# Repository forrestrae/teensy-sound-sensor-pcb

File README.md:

# Sound Sensor Teensy Carrier

A KiCad 9.0 carrier board for the Teensy 4.x microcontroller, designed for real-time audio sensing with USB-C Power Delivery input, 4S Li-ion battery management, I2S MEMS microphone, and LED lighting outputs.

## Features

- **USB-C Power Delivery** — TPS25751 PD controller with EEPROM configuration; accepts standard 5 V USB or negotiated PD voltages
- **4S Li-ion Battery System** — BQ25798 charger, BQ7791500 multi-cell protection (30 A rated), and Infineon N-channel disconnect FET
- **Regulated Power Rails** — 5 V and 3.3 V via TPS54538 synchronous buck converter
- **I2S MEMS Microphone** — TDK ICS-43434 with direct I2S2 connection to Teensy
- **Dual LED Drivers** — TPS923652 (white, ADIM + PWM) and TPS92200D2 (UV-A 3535, PWM)
- **Multi-board panel** — PCB ships as a panel; individual sub-boards extracted with kikit

## Hardware Overview

### Schematic Architecture

The design uses KiCad hierarchical sheets:

| Page | Sub-sheet | File |
|------|-----------|------|
| 1 | Top level | `Sound Sensor Teensy Carrier.kicad_sch` |
| 2 | USB-C Connector | `usb-c-connector.kicad_sch` |
| 3 | USB-PD Controller | `usb-pd-controller.kicad_sch` |
| 4 | Battery Charger | `battery-charger.kicad_sch` |
| 5 | DC Converters | `dc-converters.kicad_sch` |
| 6 | MCU | `mcu.kicad_sch` |
| 7 | Battery Protector | `battery_protector.kicad_sch` |
| 8 | Mic Boom | `mic_boom.kicad_sch` |
| 9 | WL-SUMW UV LED Board | `wl-sumw_uv_led_board.kicad_sch` |
| 10 | White LED Board | `white_led_board.kicad_sch` |

### Power Architecture

```
USB-C (5 V–20 V PD)
  └─ TPS25751 USB-PD Controller
       └─ VBUS / +5 V rail
            ├─ TPS54538 Buck → +3.3 V (MCU, logic, microphone)
            └─ BQ25798 Charger → 4S Li-ion pack (14.8 V–16.8 V)
                                    └─ BQ7791500 Protection
```

### Key Components

| Function | Part | Manufacturer |
|----------|------|--------------|
| USB-PD Controller | TPS25751DREFR | Texas Instruments |
| PD Config EEPROM | 24LC256-I/SN | Microchip |
| Battery Charger | BQ25798RQMR | Texas Instruments |
| Battery Protector | BQ7791500PWR | Texas Instruments |
| Disconnect FET | IQDH35N03LM5ATMA1 | Infineon |
| NTC Thermistor | 103AT-2 (10 kΩ) | Semitec |
| Buck Converter | TPS54538RQFR | Texas Instruments |
| MEMS Microphone | ICS-43434 | TDK |
| White LED Driver | TPS923652DRRR | Texas Instruments |
| UV LED Driver | TPS92200D2DDCR | Texas Instruments |

### MCU Connections (Teensy 4.x)

| Signal | Teensy Interface | Description |
|--------|-----------------|-------------|
| `I2S.BCLK` / `SD` / `WS` | I2S2 | ICS-43434 microphone |
| `MCU_I2C.SCL/SDA/IRQ` | I2C | Charger + PD controller |
| `LED.ONSET_EN/ADIM` | PWM | White LED onset channel |
| `LED.BEAT1_EN/ADIM` | PWM | White LED beat channel 1 |
| `LED.BEAT2_EN/ADIM` | PWM | White LED beat channel 2 |

## Repository Structure

```
Sound Sensor Teensy Carrier Kicad/
├── Sound Sensor Teensy Carrier.kicad_pro   # Project file
├── Sound Sensor Teensy Carrier.kicad_pcb   # PCB layout (panel)
├── Sound Sensor Teensy Carrier.kicad_sch   # Top-level schematic
├── battery-charger.kicad_sch
├── battery_protector.kicad_sch
├── dc-converters.kicad_sch
├── mcu.kicad_sch
├── mic_boom.kicad_sch
├── usb-c-connector.kicad_sch
├── usb-pd-controller.kicad_sch
├── white_led_board.kicad_sch
├── wl-sumw_uv_led_board.kicad_sch
├── seperate.zsh                            # kikit panel extraction script
├── ibom.config.ini                         # Interactive BOM config
└── freerouting.dsn                         # Freerouting export
```

## Tools & Dependencies

| Tool | Purpose | Install |
|------|---------|---------|
| [KiCad 9.0](https://www.kicad.org/) | EDA (schematic + layout) | kicad.org |
| [kikit](https://github.com/yaqwsx/KiKit) | Panel sub-board extraction | `pip install kikit` |
| [InteractiveHtmlBom](https://github.com/openscopeproject/InteractiveHtmlBom) | BOM generation | KiCad plugin manager |

## Sub-board Extraction

The PCB is laid out as a panel. `seperate.zsh` uses `kikit separate` to extract individual sub-boards by board-array reference designator into `output/<name>/`:

```zsh
./seperate.zsh
```

Edit the script to enable/disable specific boards (B1–B6). Extracted boards are written to `output/<board-name>/<board-name>.kicad_pcb`.

## BOM Generation

Open the project in KiCad and run the **Interactive HTML BOM** plugin. Output lands in `bom/ibom.html` per `ibom.config.ini`. Key BOM fields: Value, Footprint, MPN, Manufacturer, Datasheet, Category.

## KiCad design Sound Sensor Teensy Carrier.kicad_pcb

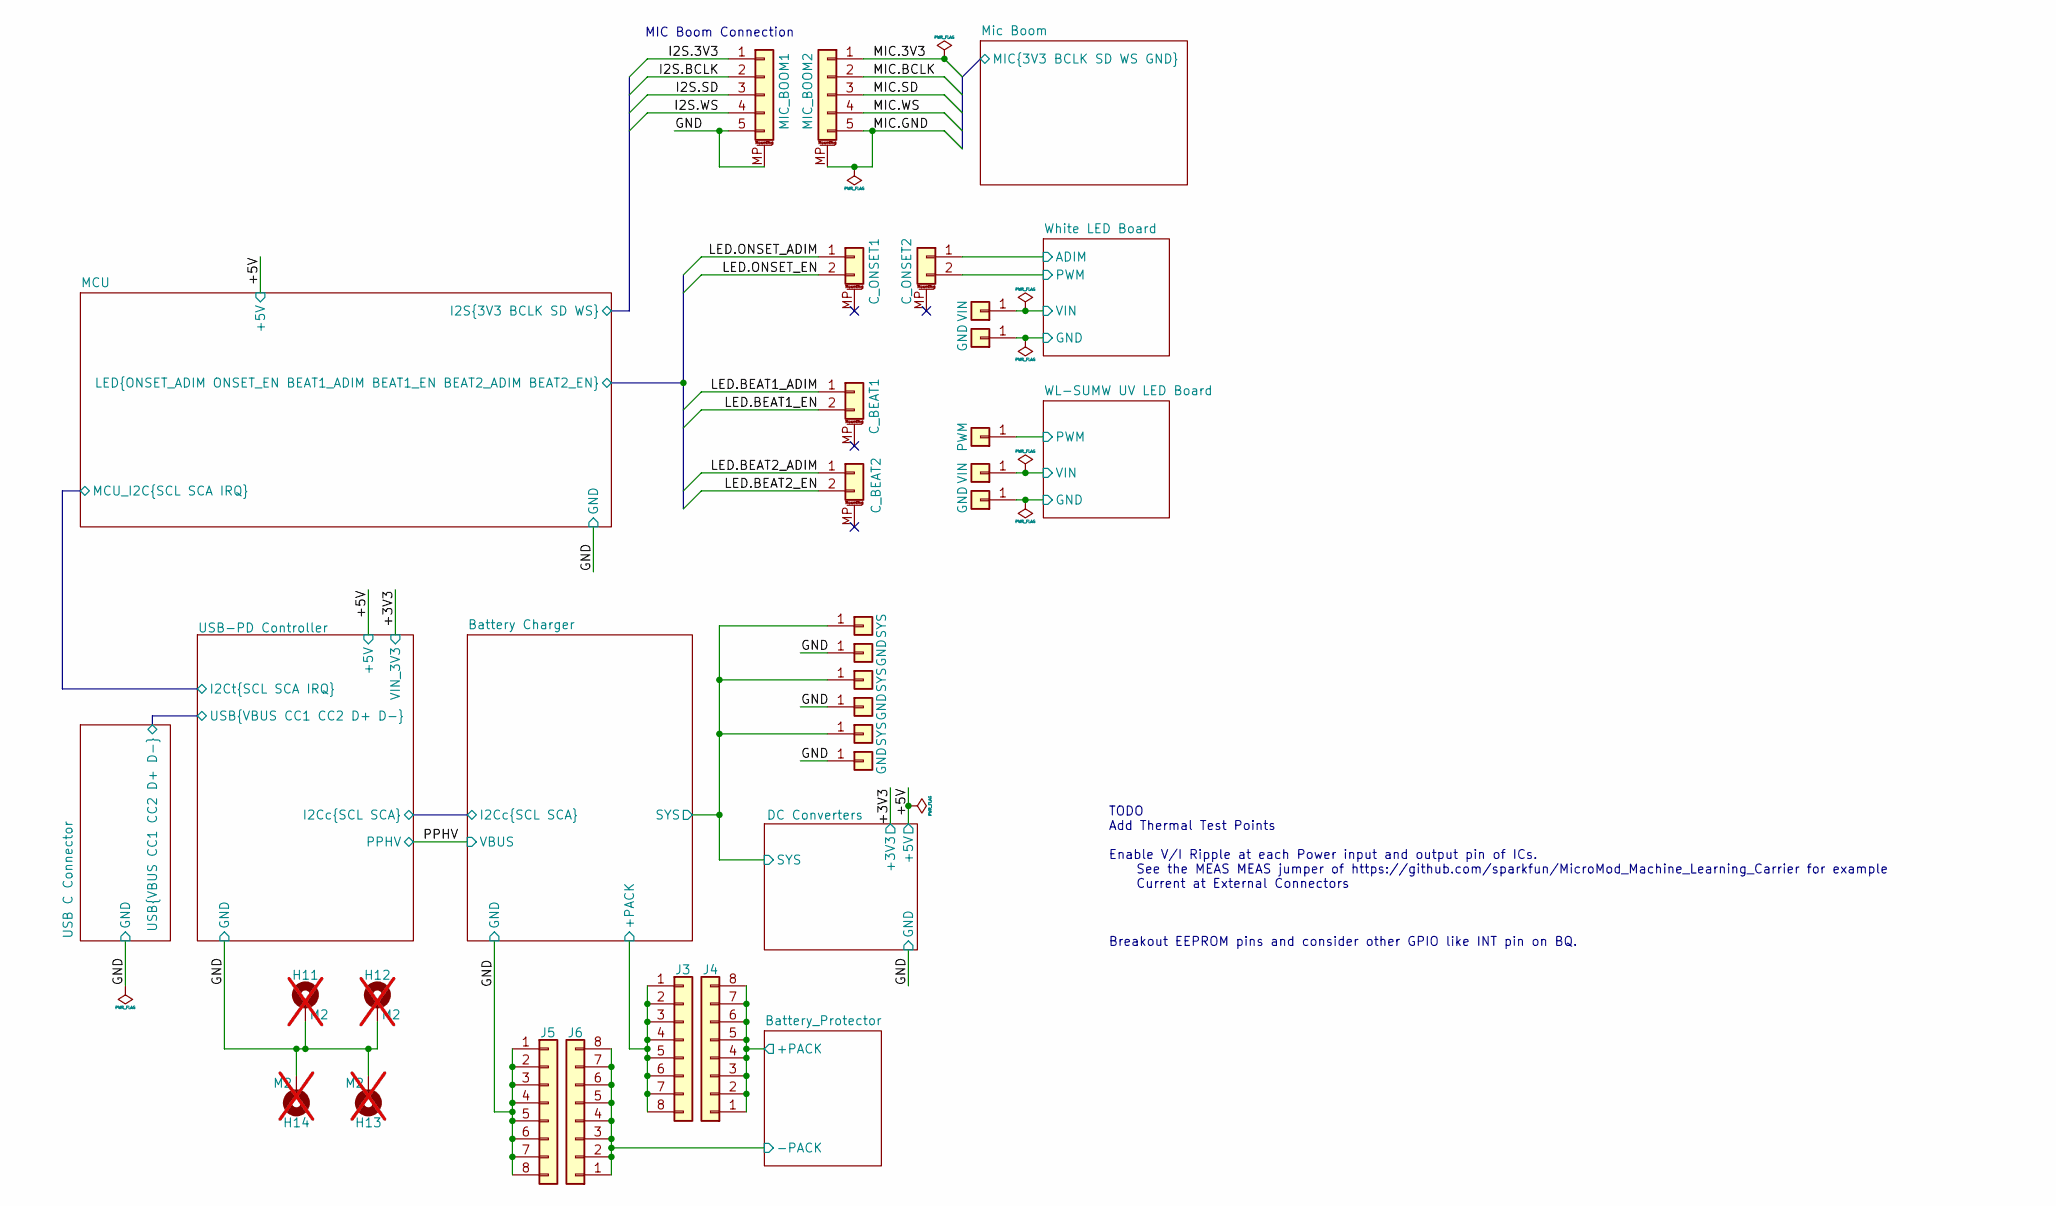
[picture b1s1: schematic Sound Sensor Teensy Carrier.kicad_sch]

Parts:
C_BEAT1: BEAT1; Molex_Pico-Clasp_203558-0207_1x02-1MP_P1.00mm_Horizontal; MPN 203558-0207; Mouser SPN 538-203558-0207
C_BEAT2: BEAT2; Molex_Pico-Clasp_203558-0207_1x02-1MP_P1.00mm_Horizontal; MPN 203558-0207; Mouser SPN 538-203558-0207
C_ONSET1, C_ONSET2: ONSET; Molex_Pico-Clasp_203558-0207_1x02-1MP_P1.00mm_Horizontal; MPN 203558-0207; Mouser SPN 538-203558-0207
H3, H5, H7: SYS; SolderWirePad_1x01_SMD_2x4mm
H4, H6, H8, H24, H26: GND; SolderWirePad_1x01_SMD_2x4mm
H11, H12, H13, H14: M2; StandOff_M2x5mm; MPN 971050244; Mouser SPN 710-971050244; not fitted
H23, H25: VIN; SolderWirePad_1x01_SMD_2x4mm
H27: PWM; SolderWirePad_1x01_SMD_1.5x3mm
J3: +PACK; SAMTEC_TMMH-104-05-F-DV; MPN TMMH-104-05-F-DV; Mouser SPN 200-TMMH10405FDV
J4: +PACK; SAMTEC_CLT-104-02-F-D; MPN CLT-104-02-F-D; Mouser SPN 200-CLT10402FD
J5: -PACK; SAMTEC_TMMH-104-05-F-DV; MPN TMMH-104-05-F-DV; Mouser SPN 200-TMMH10405FDV
J6: -PACK; SAMTEC_CLT-104-02-F-D; MPN CLT-104-02-F-D; Mouser SPN 200-CLT10402FD
MIC_BOOM1: MIC; Molex_Pico-Clasp_202396-0507_1x05-1MP_P1.00mm_Horizontal; MPN 203562-0505; Mouser SPN 538-203562-0505
MIC_BOOM2: MIC; Molex_Pico-Clasp_501331-0507_1x05-1MP_P1.00mm_Vertical; MPN 504449-0507; Mouser SPN 538-504449-0507

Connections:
/Battery Charger/+PACK: J3.1, J3.2, J3.3, J3.4, J3.5, J3.6, J3.7, J3.8; also elsewhere on the board
/Battery Charger/SYS: H3.1, H5.1, H7.1; also elsewhere on the board
/Battery_Protector/+PACK: J4.1, J4.2, J4.3, J4.4, J4.5, J4.6, J4.7, J4.8; also elsewhere on the board
/Battery_Protector/-PACK: J6.1, J6.2, J6.3, J6.4, J6.5, J6.6, J6.7, J6.8; also elsewhere on the board
/GND: H4.1, H6.1, H8.1, H11.1, H12.1, H13.1, H14.1, J5.1, J5.2, J5.3, J5.4, J5.5, J5.6, J5.7, J5.8, MIC_BOOM1.5, MIC_BOOM1.MP (MountPin); also elsewhere on the board
/MCU/I2S.3V3: MIC_BOOM1.1; also elsewhere on the board
/MCU/I2S.BCLK: MIC_BOOM1.2; also elsewhere on the board
/MCU/I2S.SD: MIC_BOOM1.3; also elsewhere on the board
/MCU/I2S.WS: MIC_BOOM1.4; also elsewhere on the board
/MCU/LED.BEAT1_ADIM: C_BEAT1.1; also elsewhere on the board
/MCU/LED.BEAT1_EN: C_BEAT1.2; also elsewhere on the board
/MCU/LED.BEAT2_ADIM: C_BEAT2.1; also elsewhere on the board
/MCU/LED.BEAT2_EN: C_BEAT2.2; also elsewhere on the board
/MCU/LED.ONSET_ADIM: C_ONSET1.1; also elsewhere on the board
/MCU/LED.ONSET_EN: C_ONSET1.2; also elsewhere on the board
/Mic Boom/MIC.3V3: MIC_BOOM2.1; also elsewhere on the board
/Mic Boom/MIC.BCLK: MIC_BOOM2.2; also elsewhere on the board
/Mic Boom/MIC.GND: MIC_BOOM2.5, MIC_BOOM2.MP (MountPin); also elsewhere on the board
/Mic Boom/MIC.SD: MIC_BOOM2.3; also elsewhere on the board
/Mic Boom/MIC.WS: MIC_BOOM2.4; also elsewhere on the board
/WL-SUMW UV LED Board/GND: H26.1; also elsewhere on the board
/WL-SUMW UV LED Board/PWM: H27.1; also elsewhere on the board
/WL-SUMW UV LED Board/VIN: H25.1; also elsewhere on the board
/White LED Board/ADIM: C_ONSET2.1; also elsewhere on the board
/White LED Board/GND: H24.1; also elsewhere on the board
/White LED Board/PWM: C_ONSET2.2; also elsewhere on the board
/White LED Board/VIN: H23.1; also elsewhere on the board

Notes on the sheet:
MIC Boom Connection
TODO Add Thermal Test Points Enable V/I Ripple at each Power input and output pin of ICs. See the MEAS MEAS jumper of https://github.com/sparkfun/MicroMod_Machine_Learning_Carrier for example Current at External Connectors Breakout EEPROM pins and consider other GPIO like INT pin on BQ.

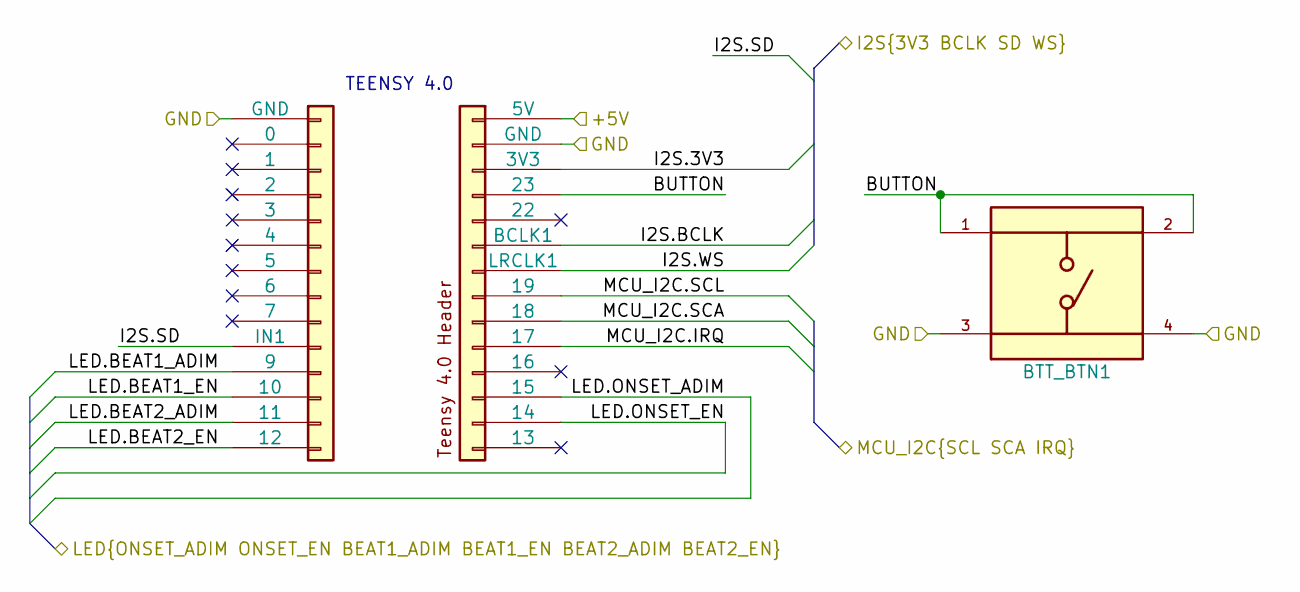
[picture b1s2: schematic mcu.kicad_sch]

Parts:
BTT_BTN1: 13mm; SW_TS02-66-130-BK-260-SCR-D; PARTREV 1.0; Mouser SPN 179-TS0266130BK260SC
C_TEENSY1: Teensy_4.0_Pin_Header; MPN SLW-150-01-G-S

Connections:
/+5V: C_TEENSY1.5V; also elsewhere on the board
/GND: BTT_BTN1.3, BTT_BTN1.4, C_TEENSY1.G0 (GND), C_TEENSY1.G1 (GND); also elsewhere on the board
/MCU/BUTTON: BTT_BTN1.1, BTT_BTN1.2, C_TEENSY1.23
/MCU/I2S.3V3: C_TEENSY1.3V3; also elsewhere on the board
/MCU/I2S.BCLK: C_TEENSY1.21 (BCLK1); also elsewhere on the board
/MCU/I2S.SD: C_TEENSY1.8 (IN1); also elsewhere on the board
/MCU/I2S.WS: C_TEENSY1.20 (LRCLK1); also elsewhere on the board
/MCU/LED.BEAT1_ADIM: C_TEENSY1.9; also elsewhere on the board
/MCU/LED.BEAT1_EN: C_TEENSY1.10; also elsewhere on the board
/MCU/LED.BEAT2_ADIM: C_TEENSY1.11; also elsewhere on the board
/MCU/LED.BEAT2_EN: C_TEENSY1.12; also elsewhere on the board
/MCU/LED.ONSET_ADIM: C_TEENSY1.15; also elsewhere on the board
/MCU/LED.ONSET_EN: C_TEENSY1.14; also elsewhere on the board
/MCU/MCU_I2C.IRQ: C_TEENSY1.17; also elsewhere on the board
/MCU/MCU_I2C.SCA: C_TEENSY1.18; also elsewhere on the board
/MCU/MCU_I2C.SCL: C_TEENSY1.19; also elsewhere on the board

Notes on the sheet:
TEENSY 4.0

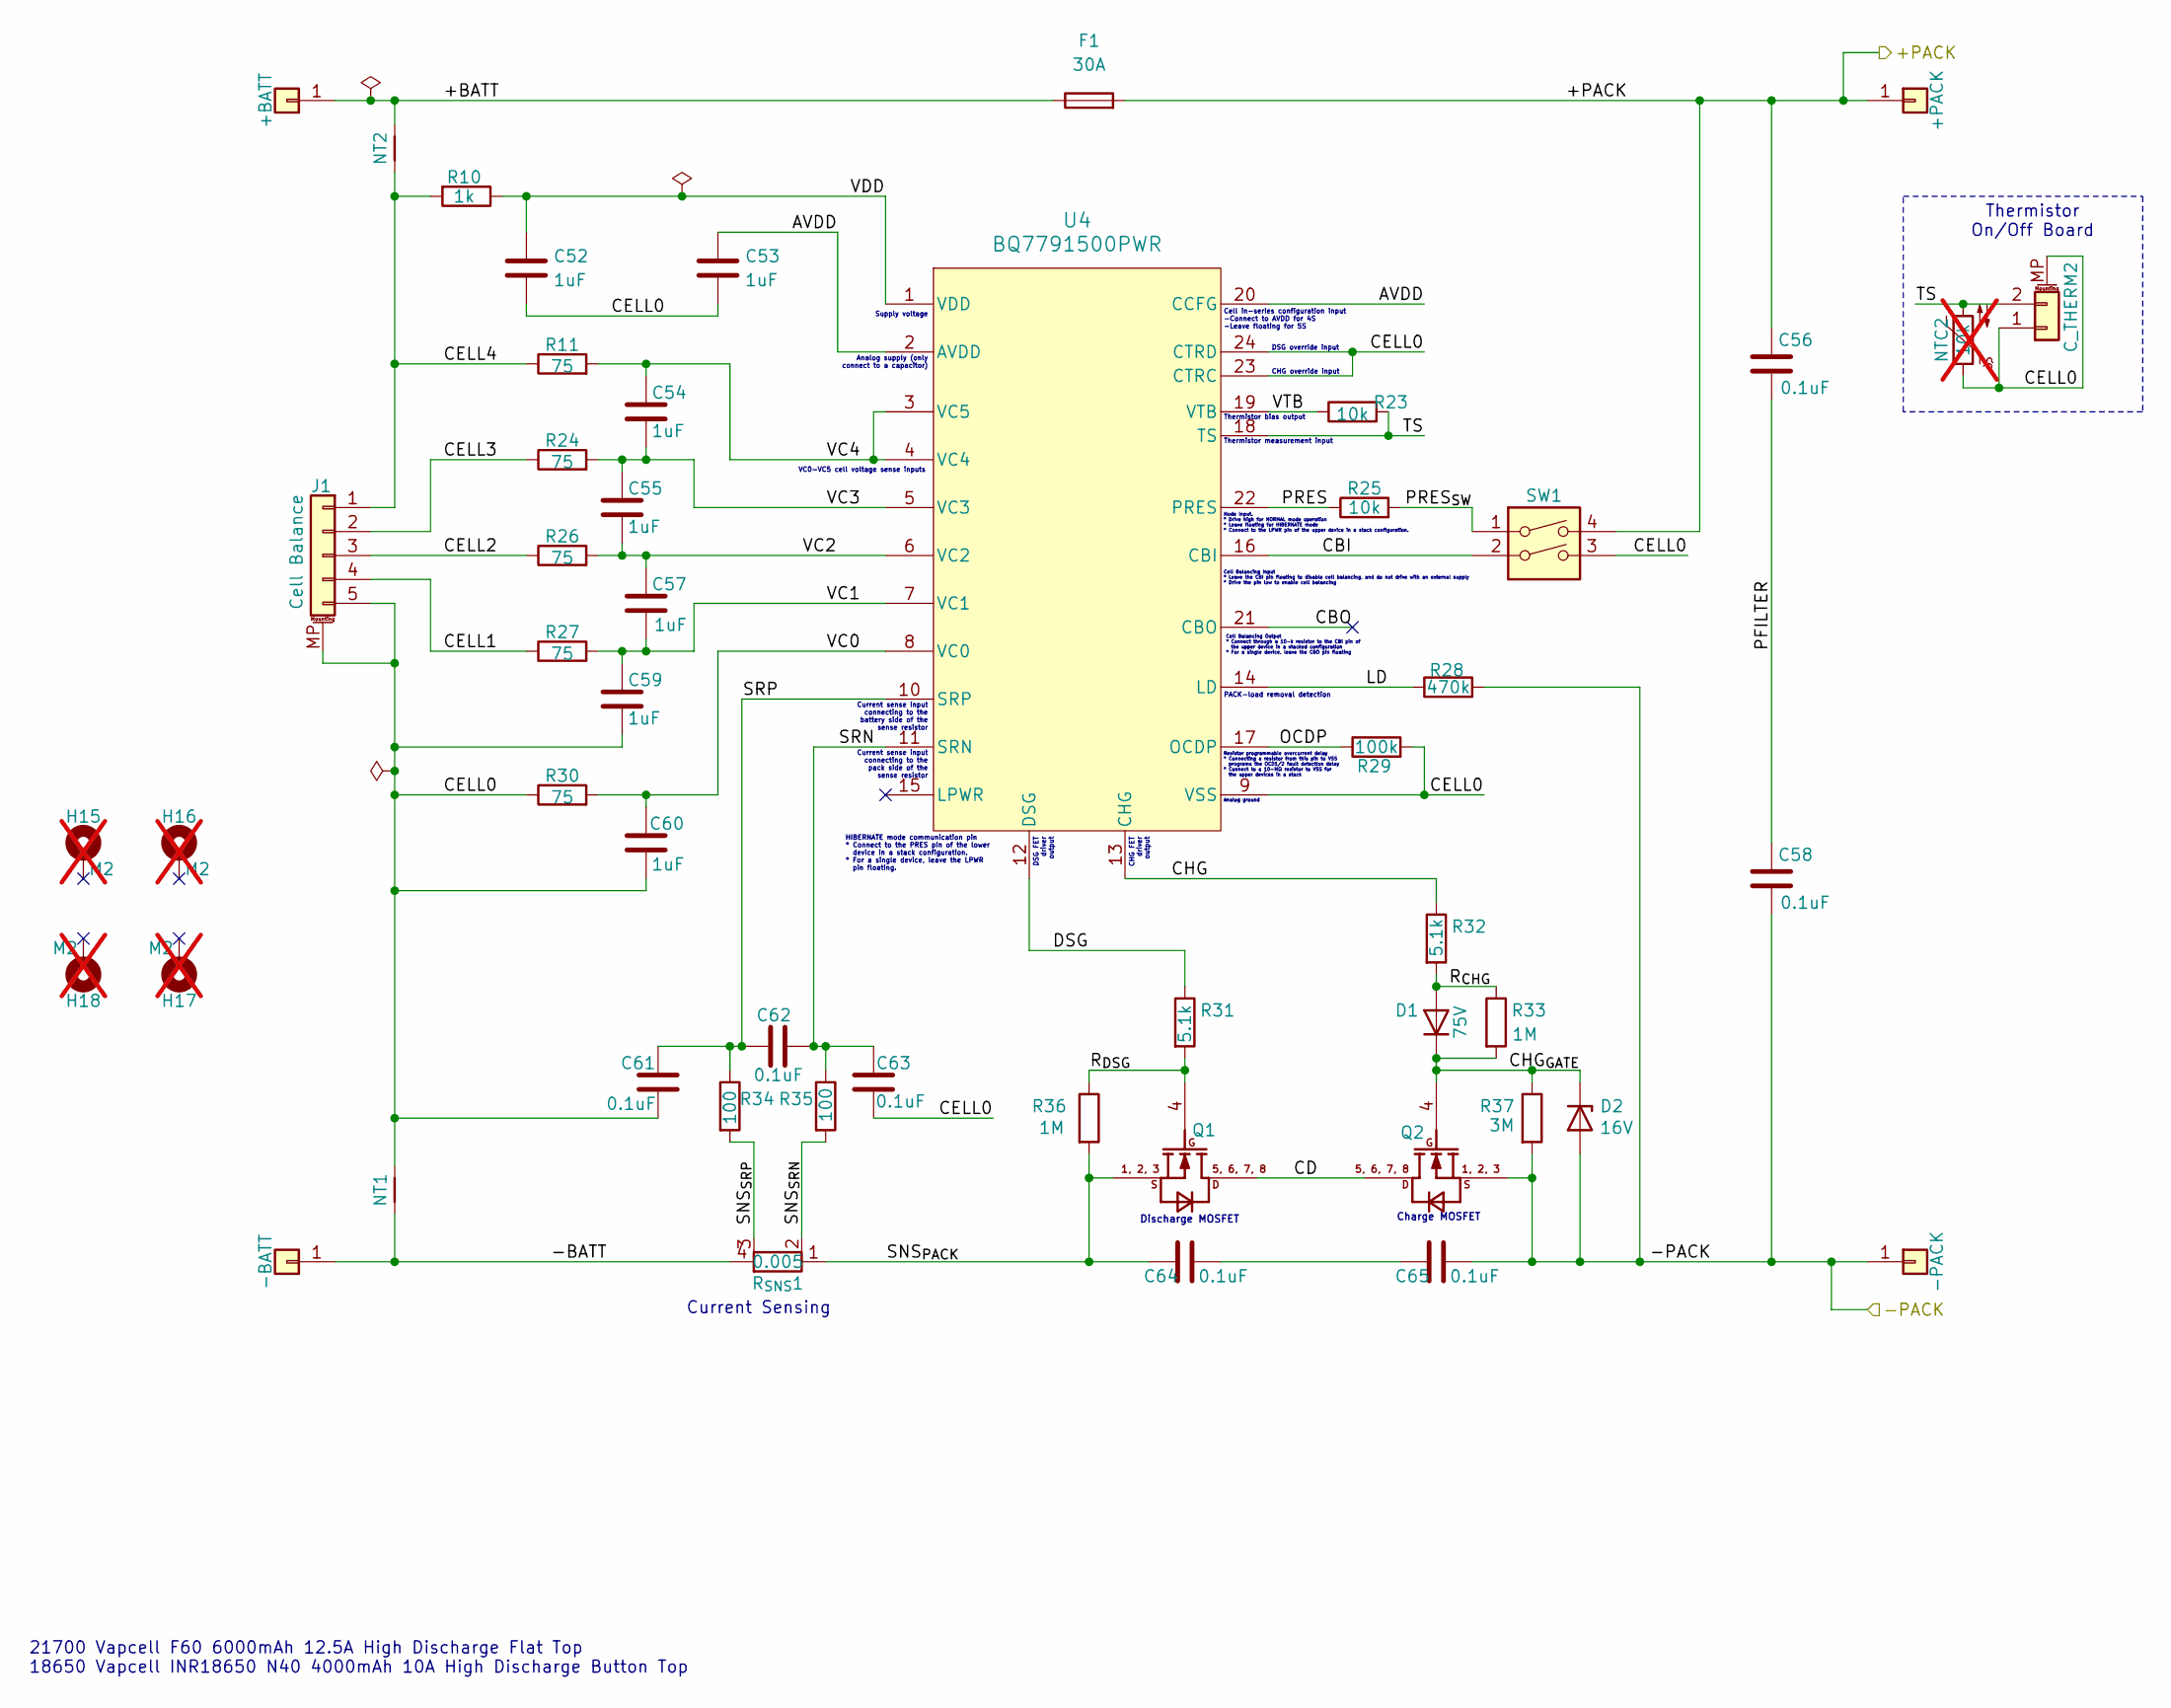
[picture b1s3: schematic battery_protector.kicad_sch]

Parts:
C52, C53, C54, C55, C57, C59, C60: 1uF; C_0603_1608Metric; MPN 06035C105KAT2A; Farnell SPN 4155078
C56, C58, C61, C62, C63, C64, C65: 0.1uF; C_0603_1608Metric; MPN GCM188R71H104KA57J; Mouser SPN 81-GCM188R71H104KA7J
C_THERM2: NTC; Molex_Pico-Clasp_203558-0207_1x02-1MP_P1.00mm_Horizontal; MPN 203558-0207; Mouser SPN 538-203558-0207
D1: 75V; D_SOD-323F; MPN CDSF4148; Mouser SPN 750-CDSF4148
D2: 16V; D_SOD-323; MPN BZX384C16-G3-08; Mouser SPN 78-BZX384C16-G3-08
F1: 30A; FUSE_SF-3812FG3000T-2; MPN SF-3812FG3000T-2; Mouser SPN 652-SF-3812FG3000T-2
H1: +BATT; SolderWirePad_1x01_SMD_4x8mm
H2: -BATT; SolderWirePad_1x01_SMD_4x8mm
H9: +PACK; SolderWirePad_1x01_SMD_4x8mm
H10: -PACK; SolderWirePad_1x01_SMD_4x8mm
H15, H16, H17, H18: M2; StandOff_M2x5mm; MPN 971050244; Mouser SPN 710-971050244; not fitted
J1: Cell Balance; Molex_Pico-Clasp_202396-0507_1x05-1MP_P1.00mm_Horizontal; MPN 203562-0505; Mouser SPN 538-203562-0505
NT1, NT2: NetTie_2; NetTie-2_SMD_Pad0.5mm
NTC2: 10k; R_0603_1608Metric; MPN NTCGS163JX103DT8; DigiKey SPN 445-NTCGS163JX103DT8CT-ND; not fitted
Q1, Q2: IQDH35N03LM5; IFX-PG-TSON-8-9-V; MPN IQDH35N03LM5ATMA1; DigiKey SPN 448-IQDH35N03LM5ATMA1TR-ND
R10: 1k; R_0603_1608Metric; MPN RCS06031K00FKEA; DigiKey SPN 541-2788-1-ND
R11, R24, R26, R27, R30: 75; R_0603_1608Metric; MPN RCS060375R0FKEA; Farnell SPN 4140951
R23, R25: 10k; R_0603_1608Metric; MPN RCS060310K0FKEA; Mouser SPN 71-RCS060310K0FKEA
R28: 470k; R_0603_1608Metric; MPN CRCW0603470KFKEA; Farnell SPN 1469814
R29: 100k; R_0603_1608Metric; MPN RCS0603100KFKEA; Mouser SPN 71-RCS0603100KFKEA
R31, R32: 5.1k; R_0603_1608Metric; MPN RCS06035K10FKEA; Farnell SPN 4140947
R33, R36: 1M; R_0603_1608Metric; MPN RCS06031M00FKEA; Farnell SPN 4140931
R34, R35: 100; R_0603_1608Metric; MPN RCS0603100RFKEA; Mouser SPN 71-RCS0603100RFKEA
R37: 3M; R_0603_1608Metric; MPN CRCW06033M00FKEA; Farnell SPN 1469650
R_{SNS}1: 0.005; R_Shunt_Vishay_WSL3637_9194Metric_T2.18mm; MPN WSL36375L000DEA; Farnell SPN 4552590
SW1: DIP; SW_DIP_SPSTx02_Slide_Omron_A6H-2101_W6.15mm_P1.27mm; MPN A6H-2101; Farnell SPN 1960885
U4: BQ7791500PWR; PW24_TEX; MPN BQ7791500PWR; DigiKey SPN 296-50995-2-ND

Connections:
/Battery_Protector/+BATT: F1.1, H1.1, NT2.2
/Battery_Protector/+PACK: C56.1, F1.2, H9.1, SW1.4; also elsewhere on the board
/Battery_Protector/-BATT: H2.1, NT1.1, R_{SNS}1.4
/Battery_Protector/-PACK: C58.2, C65.2, D2.2 (A), H10.1, Q2.1 (SOURCE), Q2.2 (SOURCE), Q2.3 (SOURCE), R28.2, R37.2; also elsewhere on the board
/Battery_Protector/AVDD: C53.1, U4.2 (AVDD), U4.20 (CCFG)
/Battery_Protector/CBI: SW1.2, U4.16 (CBI)
/Battery_Protector/CBO: U4.21 (CBO)
/Battery_Protector/CD: Q1.5 (DRAIN), Q1.6 (DRAIN), Q1.7 (DRAIN), Q1.8 (DRAIN), Q2.5 (DRAIN), Q2.6 (DRAIN), Q2.7 (DRAIN), Q2.8 (DRAIN)
/Battery_Protector/CELL0: C52.2, C53.2, C59.2, C60.2, C61.2, C63.1, C_THERM2.1, C_THERM2.MP (MountPin), J1.5, J1.MP (MountPin), NT1.2, NTC2.1, R29.2, R30.1, SW1.3, U4.9 (VSS), U4.23 (CTRC), U4.24 (CTRD)
/Battery_Protector/CELL1: J1.4, R27.1
/Battery_Protector/CELL2: J1.3, R26.1
/Battery_Protector/CELL3: J1.2, R24.1
/Battery_Protector/CELL4: J1.1, NT2.1, R10.2, R11.1
/Battery_Protector/CHG: R32.1, U4.13 (CHG)
/Battery_Protector/CHG_{GATE}: D1.1 (K), D2.1 (K), Q2.4 (GATE), R33.2, R37.1
/Battery_Protector/DSG: R31.1, U4.12 (DSG)
/Battery_Protector/LD: R28.1, U4.14 (LD)
/Battery_Protector/OCDP: R29.1, U4.17 (OCDP)
/Battery_Protector/PFILTER: C56.2, C58.1
/Battery_Protector/PRES: R25.1, U4.22 (PRES)
/Battery_Protector/PRES_{SW}: R25.2, SW1.1
/Battery_Protector/R_{CHG}: D1.2 (A), R32.2, R33.1
/Battery_Protector/R_{DSG}: Q1.4 (GATE), R31.2, R36.1
/Battery_Protector/SNS_{PACK}: C64.1, Q1.1 (SOURCE), Q1.2 (SOURCE), Q1.3 (SOURCE), R36.2, R_{SNS}1.1
/Battery_Protector/SNS_{SRN}: R35.2, R_{SNS}1.2
/Battery_Protector/SNS_{SRP}: R34.2, R_{SNS}1.3
/Battery_Protector/SRN: C62.2, C63.2, R35.1, U4.11 (SRN)
/Battery_Protector/SRP: C61.1, C62.1, R34.1, U4.10 (SRP)
/Battery_Protector/TS: C_THERM2.2, NTC2.2, R23.2, U4.18 (TS)
/Battery_Protector/VC0: C60.1, R30.2, U4.8 (VC0)
/Battery_Protector/VC1: C57.2, C59.1, R27.2, U4.7 (VC1)
/Battery_Protector/VC2: C55.2, C57.1, R26.2, U4.6 (VC2)
/Battery_Protector/VC3: C54.2, C55.1, R24.2, U4.5 (VC3)
/Battery_Protector/VC4: C54.1, R11.2, U4.3 (VC5), U4.4 (VC4)
/Battery_Protector/VDD: C52.1, R10.1, U4.1 (VDD)
/Battery_Protector/VTB: R23.1, U4.19 (VTB)
unnamed: C64.2, C65.1

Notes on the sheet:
Thermistor On/Off Board
Cell Balancing Output * Connect through a 10-k resistor to the CBI pin of the upper device in a stacked configuration * For a single device, leave the CBO pin floating
Analog ground
DSG override input
HIBERNATE mode communication pin * Connect to the PRES pin of the lower device in a stack configuration. * For a single device, leave the LPWR pin floating.
Analog supply (only connect to a capacitor)
PACK-load removal detection
Resistor programmable overcurrent delay * Connecting a resistor from this pin to VSS programs the OCD1/2 fault detection delay * Connect to a 10-MΩ resistor to VSS for the upper devices in a stack
Current Sensing
21700 Vapcell F60 6000mAh 12.5A High Discharge Flat Top 18650 Vapcell INR18650 N40 4000mAh 10A High Discharge Button Top
DSG FET driver output
Cell in-series configuration input -Connect to AVDD for 4S -Leave floating for 5S
Charge MOSFET
Cell Balancing Input * Leave the CBI pin floating to disable cell balancing, and do not drive with an external supply * Drive the pin low to enable cell balancing
Discharge MOSFET
Thermistor measurement input
CHG FET driver output
Mode Input. * Drive high for NORMAL mode operation * Leave floating for HIBERNATE mode * Connect to the LPWR pin of the upper device in a stack configuration.
Current sense input connecting to the pack side of the sense resistor
VC0-VC5 cell voltage sense inputs
Current sense input connecting to the battery side of the sense resistor
Supply voltage
Thermistor bias output
CHG override input

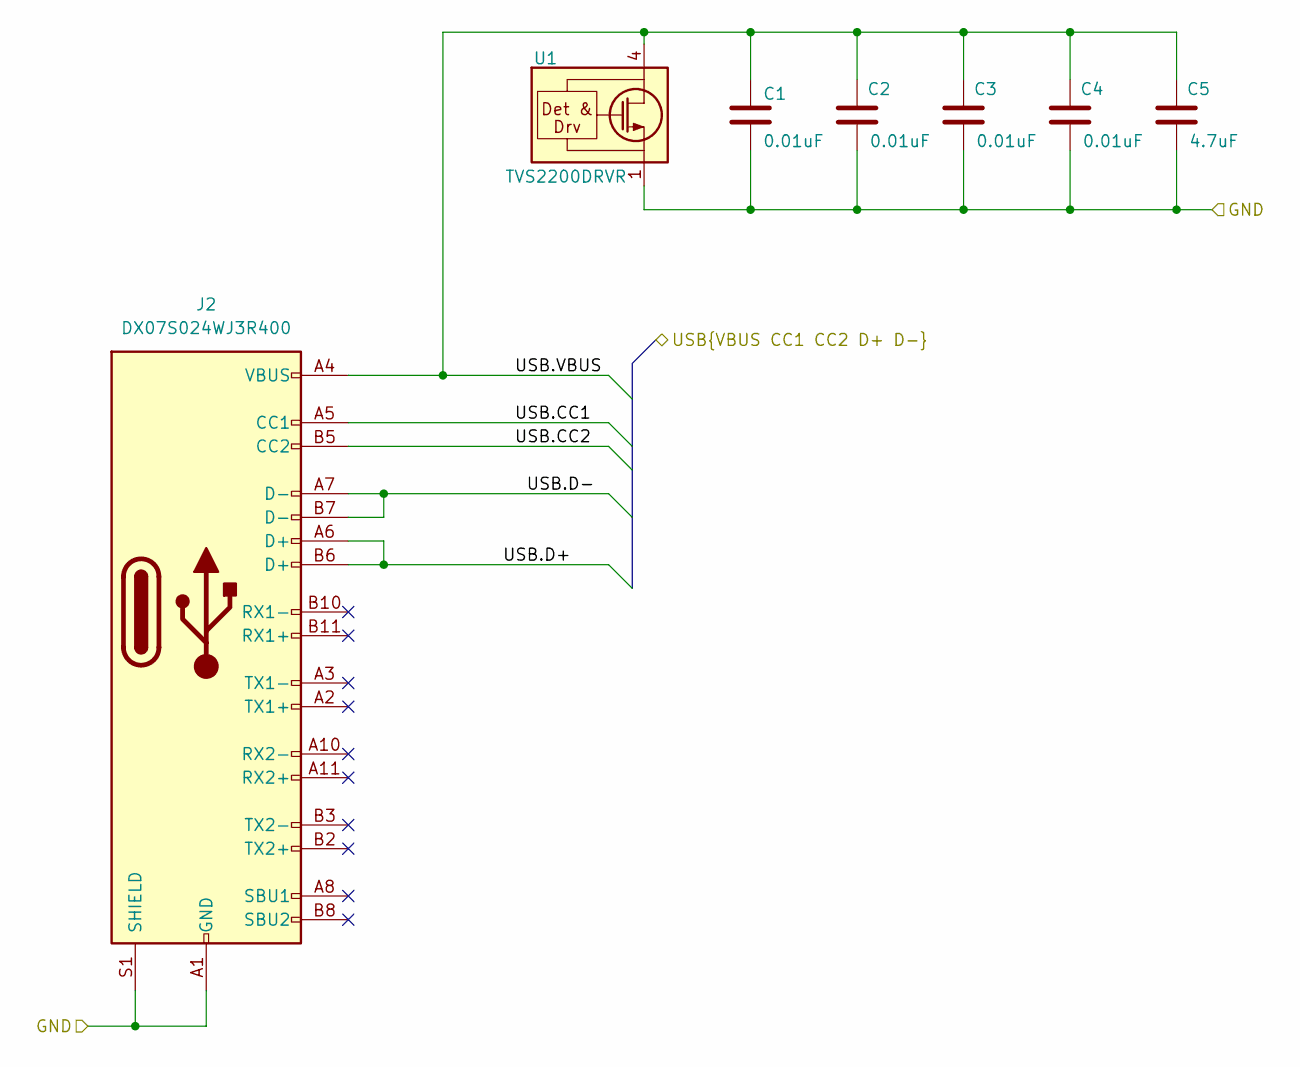
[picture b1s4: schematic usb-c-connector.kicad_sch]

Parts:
C1, C2, C3, C4: 0.01uF; C_0603_1608Metric; MPN GCM1885C1H103GA16D; Mouser SPN 81-GCM1885C1H103GA6D
C5: 4.7uF; C_0603_1608Metric; MPN GRM188R6YA475KE15D; Mouser SPN 81-GRM188R6YA475KE5D
J2: DX07S024WJ3R400; USB_C_Receptacle_JAE_DX07S024WJ3R400; MPN DX07S024WJ3R400; Mouser SPN 656-DX07S0024WJ3R400
U1: TVS2200DRVR; WSON-6-1EP_2x2mm_P0.65mm_EP1x1.6mm; MPN TVS2200DRVR; Mouser SPN 595-TVS2200DRVR

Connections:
/GND: C1.2, C2.2, C3.2, C4.2, C5.2, J2.A1 (GND), J2.A12 (GND), J2.B1 (GND), J2.B12 (GND), J2.S1 (SHIELD), U1.1 (GND), U1.2 (GND), U1.3 (GND), U1.7 (GND); also elsewhere on the board
/USB C Connector/USB.CC1: J2.A5 (CC1); also elsewhere on the board
/USB C Connector/USB.CC2: J2.B5 (CC2); also elsewhere on the board
/USB C Connector/USB.D+: J2.A6 (D+), J2.B6 (D+); also elsewhere on the board
/USB C Connector/USB.D-: J2.A7 (D-), J2.B7 (D-); also elsewhere on the board
/USB C Connector/USB.VBUS: C1.1, C2.1, C3.1, C4.1, C5.1, J2.A4 (VBUS), J2.A9 (VBUS), J2.B4 (VBUS), J2.B9 (VBUS), U1.4 (IN), U1.5 (IN), U1.6 (IN); also elsewhere on the board

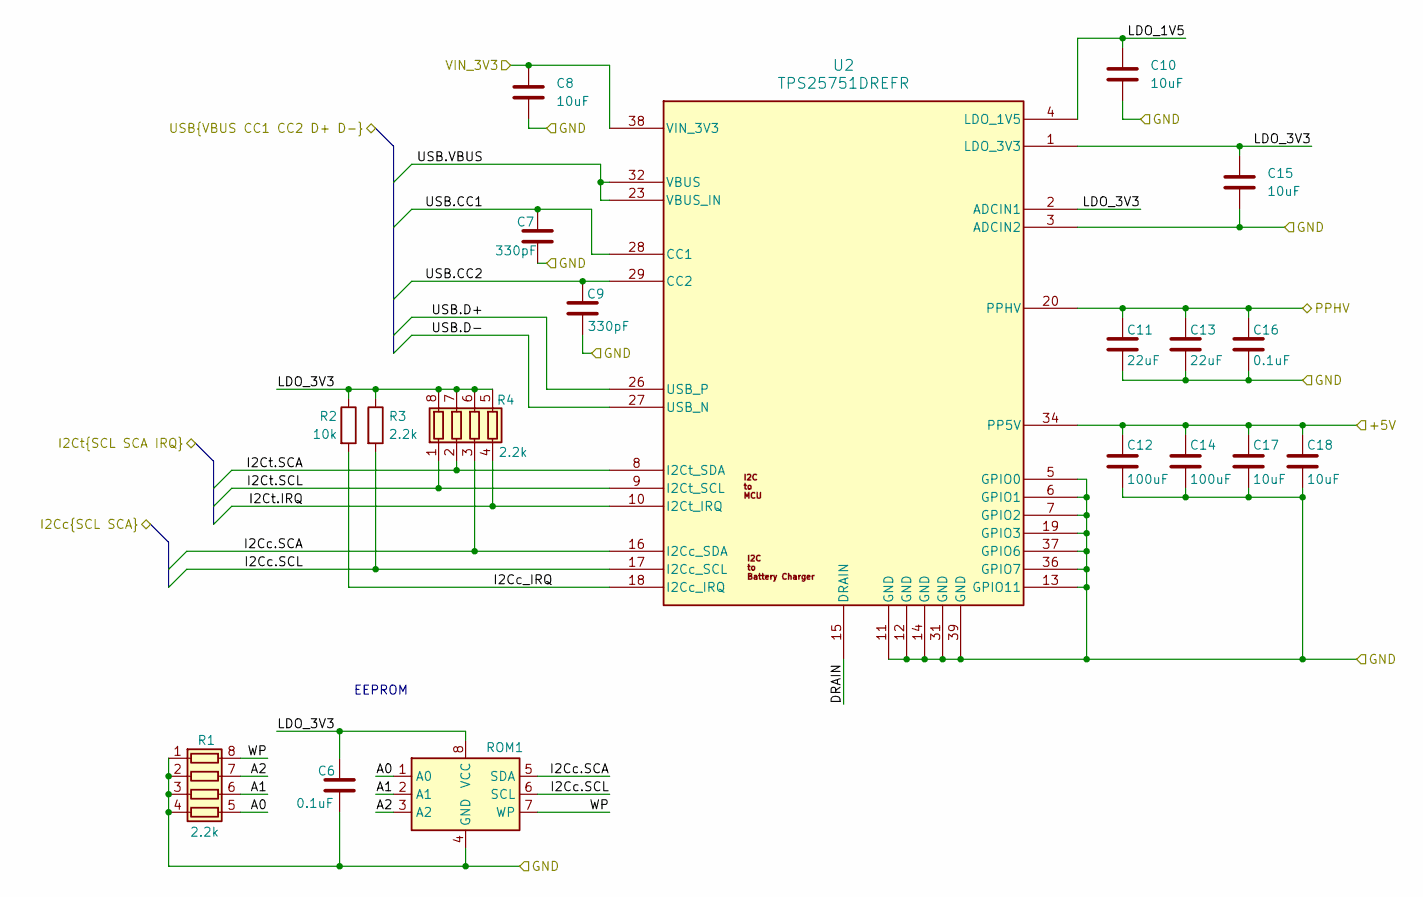
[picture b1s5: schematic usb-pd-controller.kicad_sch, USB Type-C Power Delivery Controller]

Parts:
C6, C16: 0.1uF; C_0603_1608Metric; MPN GCM188R71H104KA57J; Mouser SPN 81-GCM188R71H104KA7J
C7, C9: 330pF; C_0603_1608Metric; MPN VJ0603A331FXACW1BC; Mouser SPN 77-VJ0603A331FXACBC
C8, C10, C15, C17, C18: 10uF; C_0603_1608Metric; MPN GRM188R6YA106MA73D; Mouser SPN 81-GRM188R6YA106MA3D
C11, C13: 22uF; C_0805_2012Metric; MPN GRM21BR61E226ME44L; Mouser SPN 81-GRM21BR61E226ME4L
C12, C14: 100uF; C_1206_3216Metric; MPN CL31A107MPKNNWE; Mouser SPN 187-CL31A107MPKNNWE
R1, R4: 2.2k; R_Cat16-4; MPN CAY16-2201F4LF; Mouser SPN 652-CAY16-2201F4LF
R2: 10k; R_0603_1608Metric; MPN RCS060310K0FKEA; Mouser SPN 71-RCS060310K0FKEA
R3: 2.2k; R_0603_1608Metric; MPN RCS06032K20FKEA; Mouser SPN 71-RCS06032K20FKEA
ROM1: 24LC256-I/SN; SOIC-8_3.9x4.9mm_P1.27mm; MPN 24LC256-I/SN; Mouser SPN 579-24LC256-I/SN
U2: TPS25751DREFR; Texas_REF0038A_WQFN-38-2EP_6x4mm_P0.4; MPN TPS25751DREFR; Mouser SPN 595-TPS25751DREFR

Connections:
/+3V3: C8.1, U2.38 (VIN_3V3); also elsewhere on the board
/+5V: C12.1, C14.1, C17.1, C18.1, U2.34 (PP5V); also elsewhere on the board
/Battery Charger/I2Cc.SCA: R4.3 (R3.1), ROM1.5 (SDA), U2.16 (I2Cc_SDA); also elsewhere on the board
/Battery Charger/I2Cc.SCL: R3.2, ROM1.6 (SCL), U2.17 (I2Cc_SCL); also elsewhere on the board
/GND: C6.2, C7.2, C8.2, C9.2, C10.2, C11.2, C12.2, C13.2, C14.2, C15.2, C16.2, C17.2, C18.2, R1.1 (R1.1), R1.2 (R2.1), R1.3 (R3.1), R1.4 (R4.1), ROM1.4 (GND), U2.3 (ADCIN2), U2.5 (GPIO0), U2.6 (GPIO1), U2.7 (GPIO2), U2.11 (GND), U2.12 (GND), U2.13 (GPIO11), U2.14 (GND), U2.19 (GPIO3), U2.31 (GND), U2.36 (GPIO7), U2.37 (GPIO6), U2.39 (GND); also elsewhere on the board
/MCU/MCU_I2C.IRQ: R4.4 (R4.1), U2.10 (I2Ct_IRQ); also elsewhere on the board
/MCU/MCU_I2C.SCA: R4.2 (R2.1), U2.8 (I2Ct_SDA); also elsewhere on the board
/MCU/MCU_I2C.SCL: R4.1 (R1.1), U2.9 (I2Ct_SCL); also elsewhere on the board
/PPHV: C11.1, C13.1, C16.1, U2.20 (PPHV); also elsewhere on the board
/USB C Connector/USB.CC1: C7.1, U2.28 (CC1); also elsewhere on the board
/USB C Connector/USB.CC2: C9.1, U2.29 (CC2); also elsewhere on the board
/USB C Connector/USB.D+: U2.26 (USB_P); also elsewhere on the board
/USB C Connector/USB.D-: U2.27 (USB_N); also elsewhere on the board
/USB C Connector/USB.VBUS: U2.23 (VBUS_IN), U2.32 (VBUS); also elsewhere on the board
/USB-PD Controller/A0: R1.5 (R4.2), ROM1.1 (A0)
/USB-PD Controller/A1: R1.6 (R3.2), ROM1.2 (A1)
/USB-PD Controller/A2: R1.7 (R2.2), ROM1.3 (A2)
/USB-PD Controller/DRAIN: U2.15 (DRAIN), U2.30 (DRAIN), U2.40 (DRAIN)
/USB-PD Controller/I2Cc_IRQ: R2.2, U2.18 (I2Cc_IRQ)
/USB-PD Controller/LDO_1V5: C10.1, U2.4 (LDO_1V5)
/USB-PD Controller/LDO_3V3: C6.1, C15.1, R2.1, R3.1, R4.5 (R4.2), R4.6 (R3.2), R4.7 (R2.2), R4.8 (R1.2), ROM1.8 (VCC), U2.1 (LDO_3V3), U2.2 (ADCIN1)
/USB-PD Controller/WP: R1.8 (R1.2), ROM1.7 (WP)

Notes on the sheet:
EEPROM
